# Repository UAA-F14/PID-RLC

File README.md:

# Series RLC with Analog PID Control

Analog PID controller (op-amp based) designed to eliminate the step-response overshoot of an
underdamped series RLC circuit, documented as an honest engineering logbook: every result is marked as
calculated, simulated, or pending — no invented placeholder data. First of two related course projects;
the second applies the same PID methodology to a buck converter (see
[BUCK_1](../BUCK_1) — an earlier, IC-based adjustable buck, not the PID-controlled version required for
that follow-up project).

- **Plant:** series RLC, $f_0 \approx$ 5 kHz, $\zeta \approx 0.2$ (clearly underdamped by design)
- **Calculated:** L = 10.13 mH, R = 127.32 Ω, C = 100 nF (fixed) — predicted open-loop overshoot ≈52.7%
- **Goal:** classical PID design (root locus / pole placement) to eliminate that overshoot in closed loop

## Directory structure
```
├── design
│   └── design
│       ├── design.kicad_pcb
│       ├── design.kicad_pro
│       ├── design.kicad_sch
│       ├── readme.md
│       └── src
│           └── logFile
├── doc
│   ├── generalconfig.tex
│   ├── PY2.pdf
│   ├── PY2.tex
│   ├── Requirements.md
│   ├── Requirements.pdf
│   ├── sn-jnl.cls
│   └── src
├── LICENSE
├── README.md
├── scripts
│   ├── bode.ipynb
│   ├── design.ipynb
│   └── PID.m
└── sim
    └── RLC.asc

```

- `Design.kicad_sch` / `.kicad_pcb` / `.kicad_pro` — KiCad design
- `Design.step` — 3D model
- `requirements.pdf` — project requirements
- `PY2.pdf` — project report
- `RLC.asc` — LTspice simulation

**Photos of the built board — coming soon**

## Credit
Built as coursework with [DasReyxr](https://github.com/DasReyxr)  and [Kevin Lara](https://github.com/Gyonyu)

## License

MIT — see [LICENSE](LICENSE).

## Template
```
mkdir code design doc scripts sim src
```

```
tree >> README.md
```

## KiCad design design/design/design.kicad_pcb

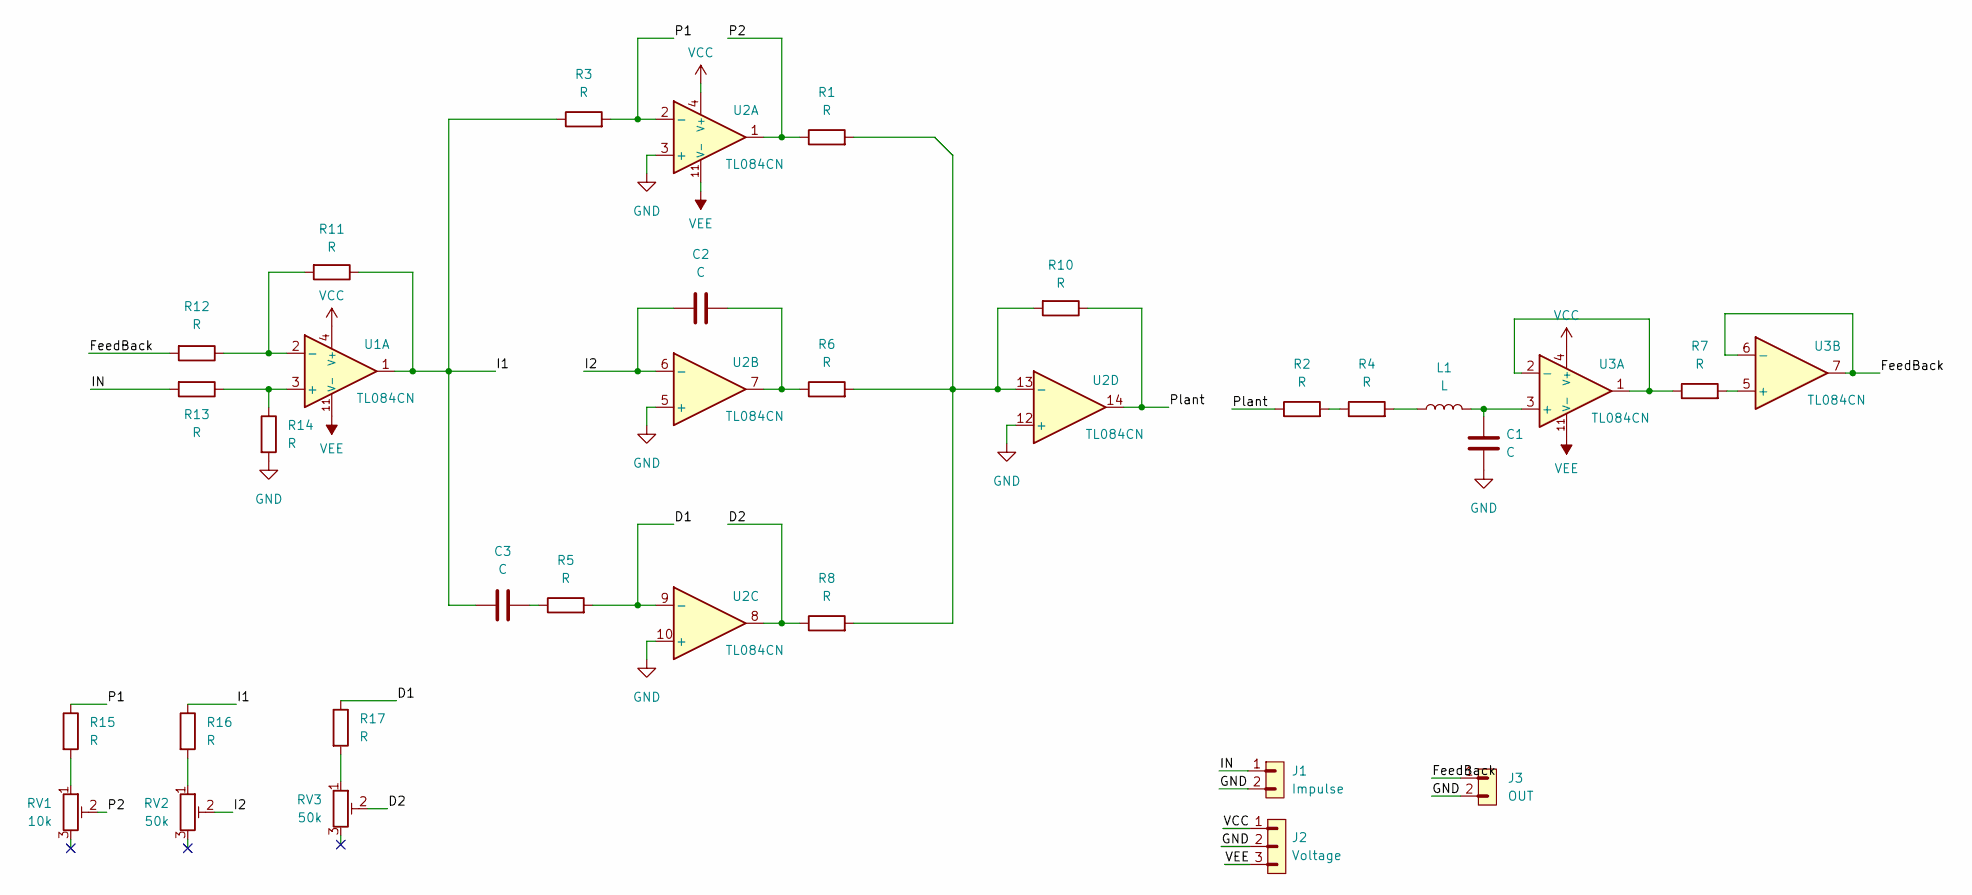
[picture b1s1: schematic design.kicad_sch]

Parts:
C1, C2, C3: C; C_Disc_D5.0mm_W2.5mm_P5.00mm
J1: Impulse; PinHeader_1x02_P2.54mm_Vertical
J2: Voltage; PinHeader_1x03_P2.54mm_Vertical
J3: OUT; PinHeader_1x02_P2.54mm_Vertical
L1: L; L_Radial_D7.5mm_P3.50mm_Fastron_07P
R1, R2, R3, R4, R5, R6, R7, R8, R10, R11, R12, R13, R14, R15, R16, R17: R; R_Axial_DIN0207_L6.3mm_D2.5mm_P10.16mm_Horizontal
RV1: 10k; Potentiometer_Bourns_3296W_Vertical
RV2, RV3: 50k; Potentiometer_Bourns_3296W_Vertical
U1, U2, U3: TL084CN; DIP-14_W7.62mm_LongPads

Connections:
/D1: R5.2, R17.1, U2.9 (-)
/D2: R8.1, RV3.2, U2.8
/FeedBack: J3.1, R12.2, U3.6 (-), U3.7
/I1: C3.1, R3.1, R11.1, R16.1, U1.1
/I2: C2.1, RV2.2, U2.6 (-)
/IN: J1.1, R13.2
/P1: R3.2, R15.1, U2.2 (-)
/P2: R1.1, RV1.2, U2.1
/Plant: R2.1, R10.1, U2.14
GND: C1.1, J1.2, J2.2, J3.2, R14.2, U2.3 (+), U2.5 (+), U2.10 (+), U2.12 (+); also elsewhere on the board
unnamed: C2.2, R6.1, U2.7
unnamed: C3.2, R5.1
unnamed: L1.1, R4.2
unnamed: R2.2, R4.1
unnamed: R15.2, RV1.1
unnamed: R16.2, RV2.1
unnamed: R17.2, RV3.1
unnamed: R13.1, R14.1, U1.3 (+)
unnamed: R11.2, R12.1, U1.2 (-)
unnamed: R1.2, R6.2, R8.2, R10.2, U2.13 (-)
unnamed: C1.2, L1.2, U3.3 (+)
unnamed: R7.1, U3.1, U3.2 (-)
unnamed 22: R7.2, U3.5 (+); also elsewhere on the board
VCC: J2.1, U1.4 (V+), U2.4 (V+), U3.4 (V+)
VEE: J2.3, U1.11 (V-), U2.11 (V-), U3.11 (V-)

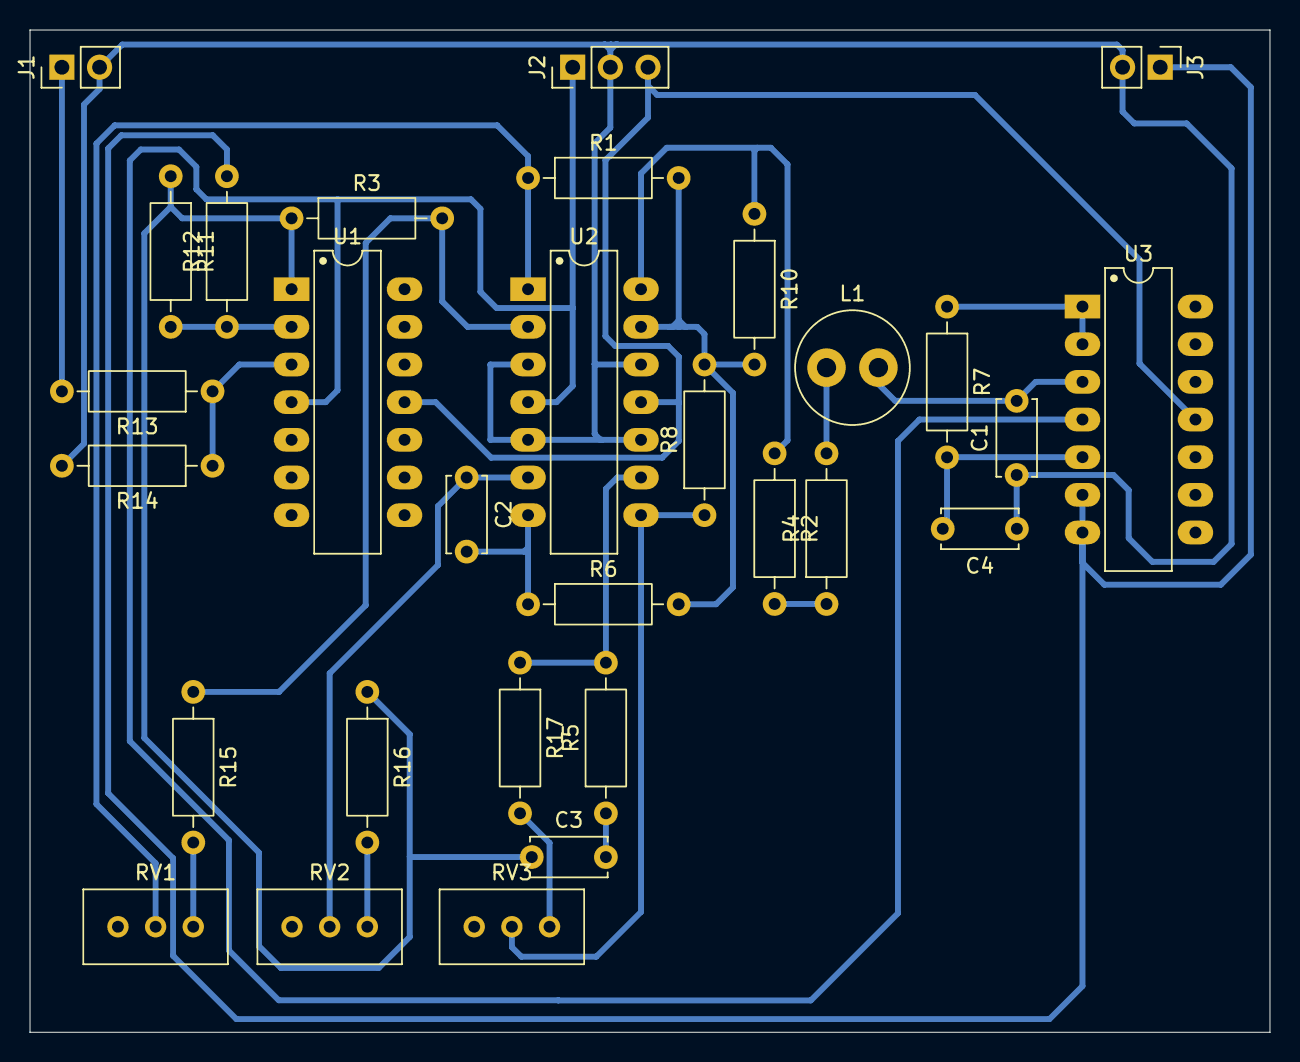
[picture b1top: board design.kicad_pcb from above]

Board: 2 copper layers, 83.6 x 67.6 mm, 30 parts (0 on the bottom side), 25 nets.

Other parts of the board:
C4: C; C_Disc_D5.0mm_W2.5mm_P5.00mm

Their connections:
GND: C4.1; also elsewhere on the board
unnamed 22: C4.2; also elsewhere on the board
